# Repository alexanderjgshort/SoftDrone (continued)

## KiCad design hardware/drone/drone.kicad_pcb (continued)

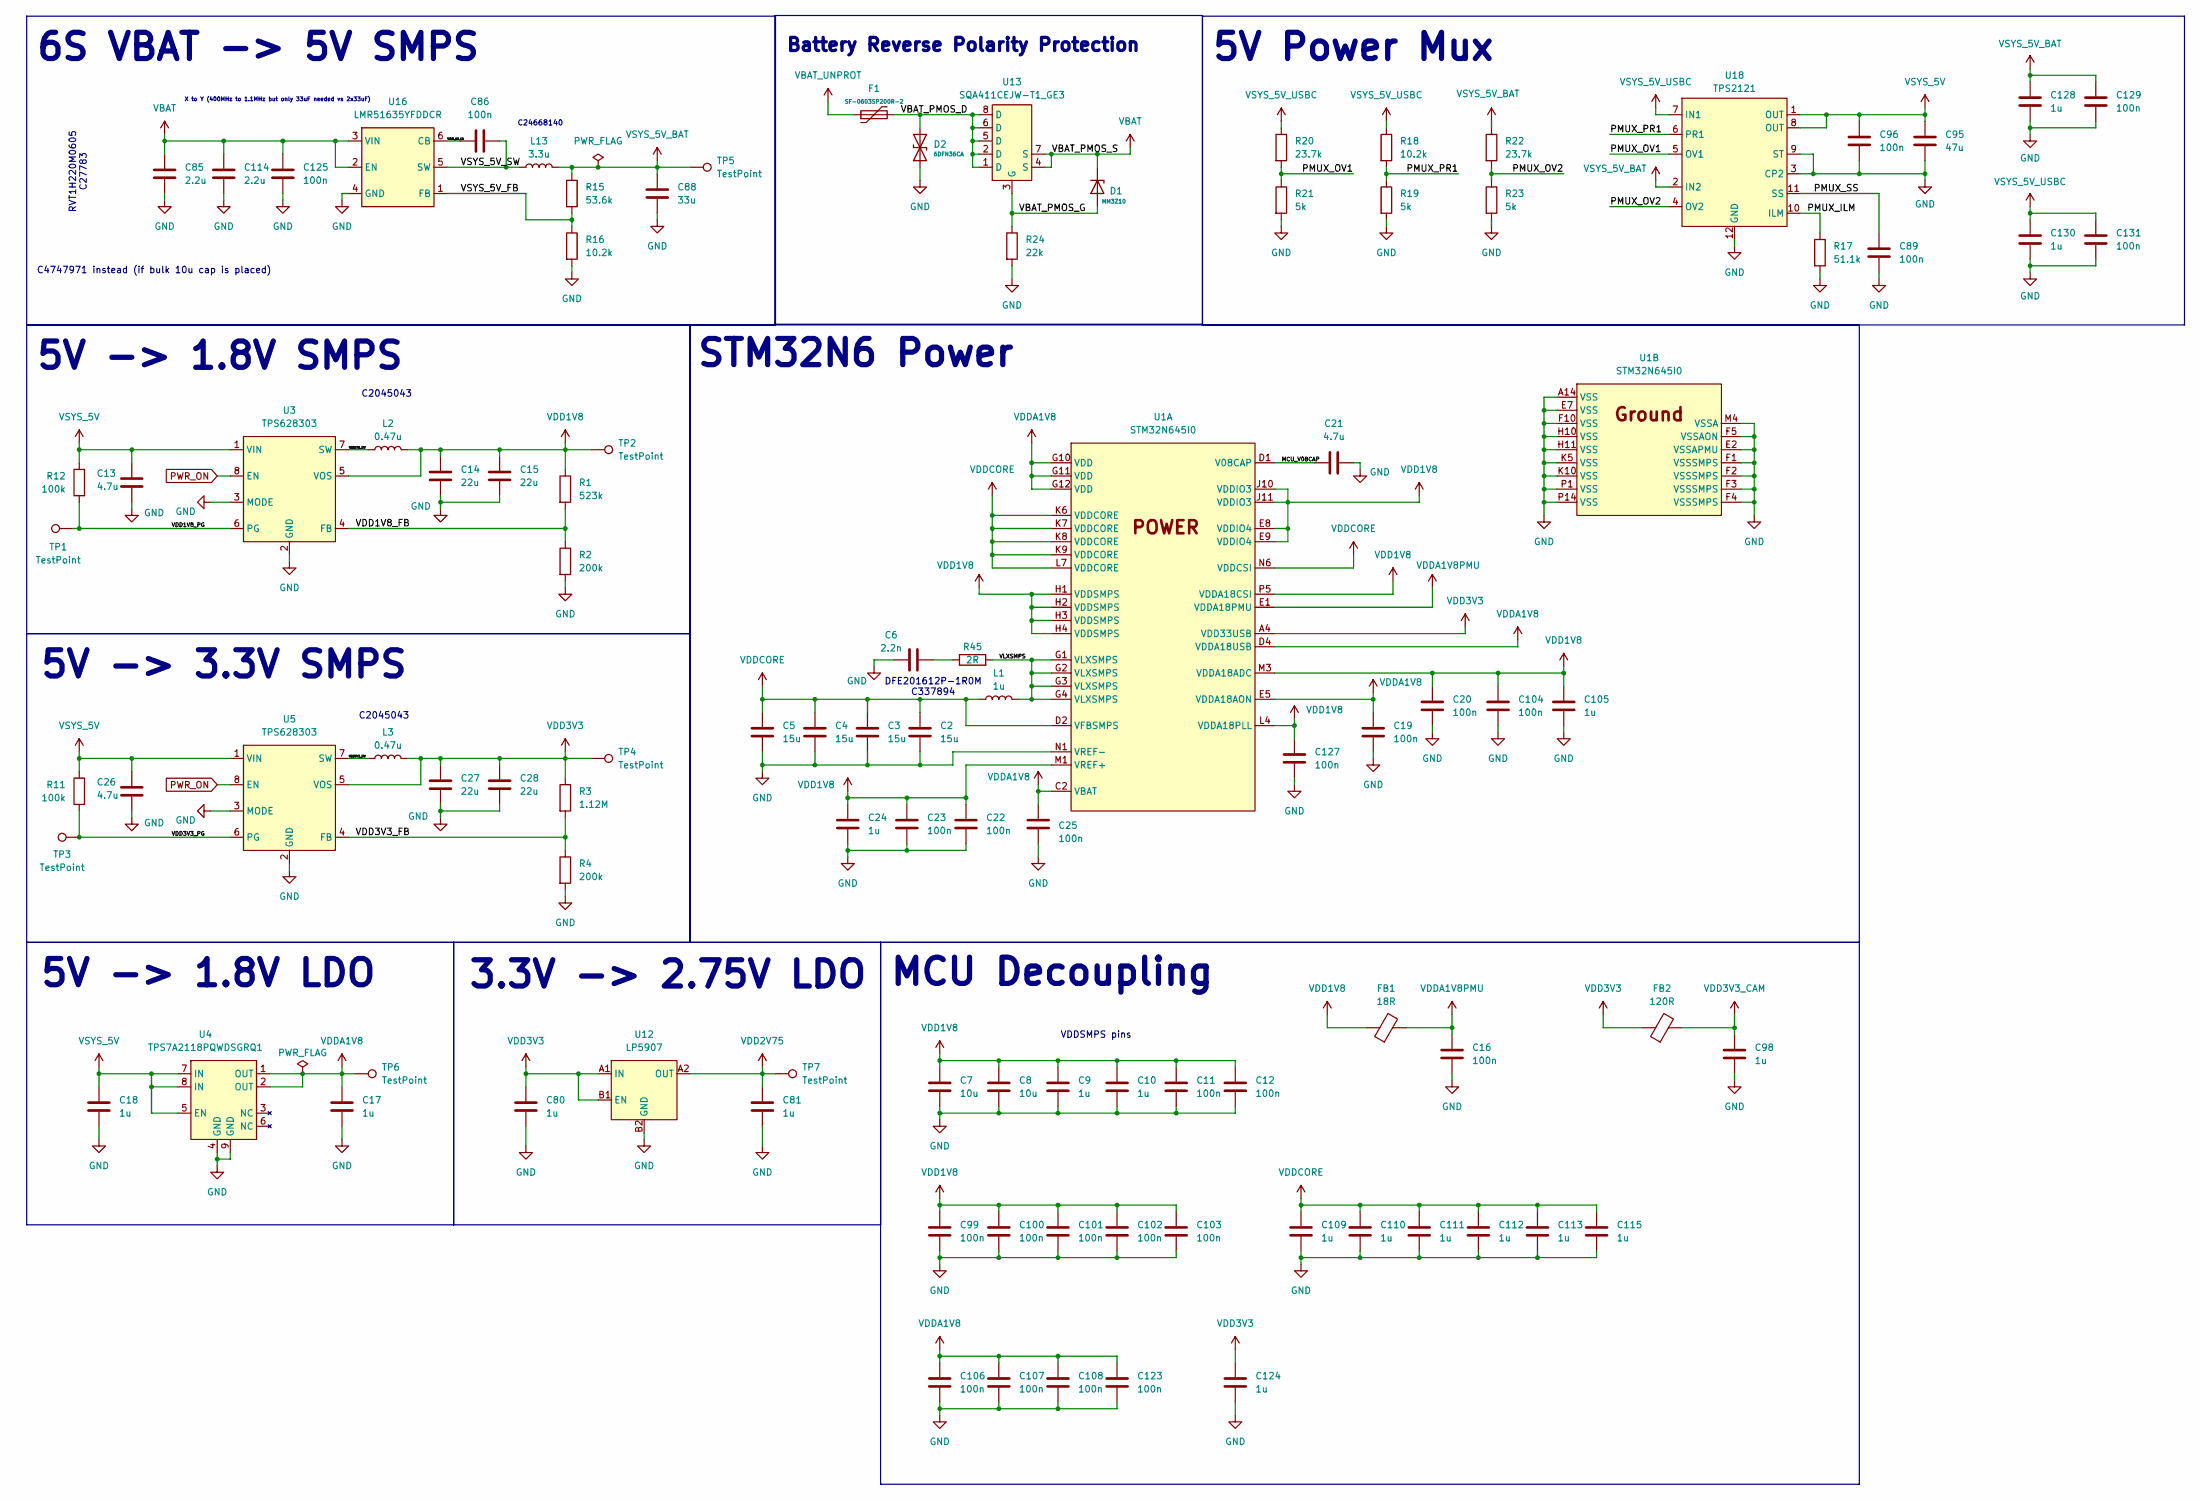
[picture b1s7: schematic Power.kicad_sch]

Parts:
C2, C3, C4, C5: 15u; C_0603_1608Metric
C6: 2.2n; C_0402_1005Metric
C7, C8: 10u; C_0402_1005Metric
C9, C10, C24, C105, C109, C110, C111, C112, C113, C115: 1u; C_0201_0603Metric
C11, C12, C16, C19, C20, C22, C23, C25, C99, C100, C101, C102, C103, C104, C106, C107, C108, C123, C127: 100n; C_0201_0603Metric
C13, C26: 4.7u; C_0603_1608Metric
C14, C15, C27, C28: 22u; C_0603_1608Metric
C17, C18, C80, C81, C128, C130: 1u; C_0603_1608Metric
C21: 4.7u; C_0402_1005Metric
C85, C114: 2.2u; C_1206_3216Metric
C86, C89, C96, C125: 100n; C_0603_1608Metric
C88: 33u; C_1812_4532Metric
C95: 47u; C_1206_3216Metric
C98, C124: 1u; C_0402_1005Metric
C129, C131: 100n; C_0402_1005Metric
D1: MM3Z10; D_SOD-323
D2: 6DFN36CA; 6DFN12CA
F1: SF-0603SP200R-2; Fuse_0603_1608Metric
FB1: 18R; R_0603_1608Metric
FB2: 120R; R_0402_1005Metric
L1: 1u; CVH201610A-2R2M
L2, L3: 0.47u; TFM201610ALC-R47MTAA
L13: 3.3u; 74439324033
R1: 523k; R_0402_1005Metric
R2, R4: 200k; R_0402_1005Metric
R3: 1.12M; R_0402_1005Metric
R11, R12: 100k; R_0402_1005Metric
R15: 53.6k; R_0603_1608Metric
R16: 10.2k; R_0603_1608Metric
R17: 51.1k; R_0402_1005Metric
R18: 10.2k; R_0402_1005Metric
R19, R21, R23: 5k; R_0402_1005Metric
R20, R22: 23.7k; R_0402_1005Metric
R24: 22k; R_0603_1608Metric
R45: 2R; R_0402_1005Metric
TP1, TP2, TP3, TP4, TP5, TP6, TP7: TestPoint; TestPoint_Pad_2.0x2.0mm
U1: STM32N645I0; BGA178C80P14X14_1200X1200X100
U3, U5: TPS628303; WQFN-HR8_RZE_TEX
U4: TPS7A2118PQWDSGRQ1; Texas_DSG0008A_WSON-8-1EP_2x2mm_P0.5mm_EP0.9x1.6mm
U12: LP5907; BGA4C35P2X2_64X64X50
U13: SQA411CEJW-T1_GE3; SQA411CEJWT1_GE3
U16: LMR51635YFDDCR; SOT-23-6
U18: TPS2121; TPS2121RUXT

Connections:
/Power/MCU_V08CAP: C21.2, U1.D1 (V08CAP)
/Power/PMUX_ILM: R17.1, U18.10 (ILM)
/Power/PMUX_OV1: R20.2, R21.1, U18.5 (OV1)
/Power/PMUX_OV2: R22.2, R23.1, U18.4 (OV2)
/Power/PMUX_PR1: R18.2, R19.1, U18.6 (PR1)
/Power/PMUX_SS: C89.1, U18.11 (SS)
/Power/VBAT_PMOS_D: D2.2 (A2), F1.2, U13.1 (D), U13.2 (D), U13.5 (D), U13.6 (D), U13.8 (D)
/Power/VBAT_PMOS_G: D1.2 (A), R24.1, U13.3 (G)
/Power/VDD1V8_FB: R1.2, R2.1, U3.4 (FB)
/Power/VDD1V8_PG: R12.2, TP1.1 (1_1), U3.6 (PG)
/Power/VDD1V8_SW: L2.1, U3.7 (SW)
/Power/VDD3V3_FB: R3.2, R4.1, U5.4 (FB)
/Power/VDD3V3_PG: R11.2, TP3.1 (1_1), U5.6 (PG)
/Power/VDD3V3_SW: L3.1, U5.7 (SW)
/Power/VLXSMPS: L1.2, R45.2, U1.G1 (VLXSMPS), U1.G2 (VLXSMPS), U1.G3 (VLXSMPS), U1.G4 (VLXSMPS)
/Power/VSYS_5V_CB: C86.1, U16.6 (CB)
/Power/VSYS_5V_FB: R15.2, R16.1, U16.1 (FB)
/Power/VSYS_5V_SW: C86.2, L13.1, U16.5 (SW)
GND: C2.2, C3.2, C4.2, C5.2, C6.1, C7.2, C8.2, C9.2, C10.2, C11.2, C12.2, C13.2, C14.2, C15.2, C16.2, C17.2, C18.2, C19.2, C20.2, C21.1, C22.2, C23.2, C24.2, C25.2, C26.2, C27.2, C28.2, C80.2, C81.2, C85.2, C88.2, C89.2, C95.2, C96.2, C98.2, C99.2, C100.2, C101.2, C102.2, C103.2, C104.2, C105.2, C106.2, C107.2, C108.2, C109.2, C110.2, C111.2, C112.2, C113.2, C114.2, C115.2, C123.2, C124.2, C125.2, C127.2, C128.2, C129.2, C130.2, C131.2, D2.1 (A1), R2.2, R4.2, R16.2, R17.2, R19.2, R21.2, R23.2, R24.2, U1.A14 (VSS), U1.E2 (VSSAPMU), U1.E7 (VSS), U1.F1 (VSSSMPS), U1.F2 (VSSSMPS), U1.F3 (VSSSMPS), U1.F4 (VSSSMPS), U1.F5 (VSSAON), U1.F10 (VSS), U1.H10 (VSS), U1.H11 (VSS), U1.K5 (VSS), U1.K10 (VSS), U1.M4 (VSSA), U1.N1 (VREF-), U1.P1 (VSS), U1.P14 (VSS), U3.2 (GND), U3.3 (MODE), U4.4 (GND), U4.9 (GND), U5.2 (GND), U5.3 (MODE), U12.B2 (GND), U16.4 (GND), U18.3 (CP2), U18.9 (ST), U18.12 (GND); also elsewhere on the board
unnamed: C6.2, R45.1
PWR_ON: U3.8 (EN), U5.8 (EN); also elsewhere on the board
VBAT: C85.1, C114.1, C125.1, D1.1 (K), U13.4 (S), U13.7 (S), U16.2 (EN), U16.3 (VIN); also elsewhere on the board
VBAT_UNPROT: F1.1; also elsewhere on the board
VDD1V8: C7.1, C8.1, C9.1, C10.1, C11.1, C12.1, C14.1, C15.1, C20.1, C22.1, C23.1, C24.1, C99.1, C100.1, C101.1, C102.1, C103.1, C104.1, C105.1, C127.1, FB1.1, L2.2, R1.1, TP2.1 (1_1), U1.E8 (VDDIO4), U1.E9 (VDDIO4), U1.H1 (VDDSMPS), U1.H2 (VDDSMPS), U1.H3 (VDDSMPS), U1.H4 (VDDSMPS), U1.J10 (VDDIO3), U1.J11 (VDDIO3), U1.L4 (VDDA18PLL), U1.M1 (VREF+), U1.M3 (VDDA18ADC), U1.P5 (VDDA18CSI), U3.5 (VOS); also elsewhere on the board
VDD2V75: C81.1, TP7.1 (1_1), U12.A2 (OUT); also elsewhere on the board
VDD3V3: C27.1, C28.1, C80.1, C124.1, FB2.1, L3.2, R3.1, TP4.1 (1_1), U1.A4 (VDD33USB), U5.5 (VOS), U12.A1 (IN), U12.B1 (EN); also elsewhere on the board
VDD3V3_CAM: C98.1, FB2.2; also elsewhere on the board
VDDA1V8: C17.1, C19.1, C25.1, C106.1, C107.1, C108.1, C123.1, TP6.1 (1_1), U1.C2 (VBAT), U1.D4 (VDDA18USB), U1.E5 (VDDA18AON), U1.G10 (VDD), U1.G11 (VDD), U1.G12 (VDD), U4.1 (OUT), U4.2 (OUT); also elsewhere on the board
VDDA1V8PMU: C16.1, FB1.2, U1.E1 (VDDA18PMU)
VDDCORE: C2.1, C3.1, C4.1, C5.1, C109.1, C110.1, C111.1, C112.1, C113.1, C115.1, L1.1, U1.D2 (VFBSMPS), U1.K6 (VDDCORE), U1.K7 (VDDCORE), U1.K8 (VDDCORE), U1.K9 (VDDCORE), U1.L7 (VDDCORE), U1.N6 (VDDCSI)
VSYS_5V: C13.1, C18.1, C26.1, C95.1, C96.1, R11.1, R12.1, U3.1 (VIN), U4.5 (EN), U4.7 (IN), U4.8 (IN), U5.1 (VIN), U18.1 (OUT), U18.8 (OUT); also elsewhere on the board
VSYS_5V_BAT: C88.1, C128.1, C129.1, L13.2, R15.1, R22.1, TP5.1 (1_1), U18.2 (IN2)
VSYS_5V_USBC: C130.1, C131.1, R18.1, R20.1, U18.7 (IN1); also elsewhere on the board

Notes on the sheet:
3.3V -> 2.75V LDO
DFE201612P-1R0M C337894
RVT1H220M0605 C27783
5V -> 1.8V LDO
VDDSMPS pins
C2045043
5V Power Mux
MCU Decoupling
Battery Reverse Polarity Protection
C4747971 instead (if bulk 10u cap is placed)
5V -> 3.3V SMPS
6S VBAT -> 5V SMPS
5V -> 1.8V SMPS
X to Y (400MHz to 1.1MHz but only 33uF needed vs 2x33uF)
C24668140
STM32N6 Power

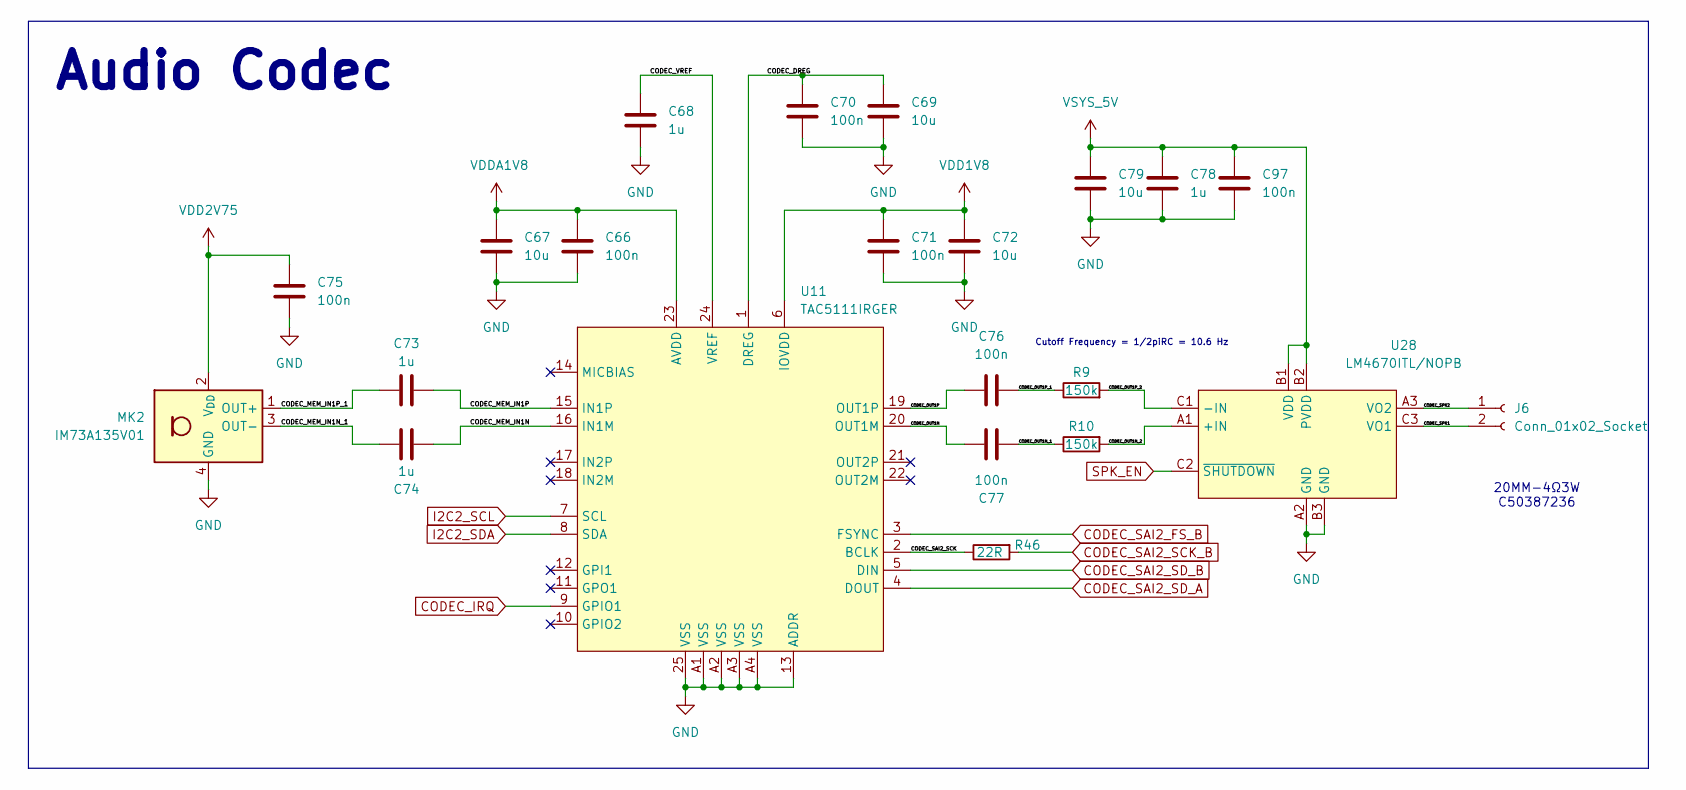
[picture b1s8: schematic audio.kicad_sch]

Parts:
C66, C70, C71, C75, C97: 100n; C_0402_1005Metric
C67, C69, C72, C79: 10u; C_0805_2012Metric
C68: 1u; C_0603_1608Metric
C73, C74, C78: 1u; C_0402_1005Metric
C76, C77: 100n; C_0201_0603Metric
J6: Conn_01x02_Socket; JST_SH_BM02B-SRSS-TB_1x02-1MP_P1.00mm_Vertical
MK2: IM73A135V01; Infineon_PG-LLGA-5-2
R9, R10: 150k; R_0201_0603Metric
R46: 22R; R_0402_1005Metric
U11: TAC5111IRGER
U28: LM4670ITL/NOPB; BGA9C50P3X3_146X148X68

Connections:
/Audio/CODEC_DREG: C69.1, C70.1, U11.1 (DREG)
/Audio/CODEC_MEM_IN1N: C74.2, U11.16 (IN1M)
/Audio/CODEC_MEM_IN1N_1: C74.1, MK2.3 (OUT-)
/Audio/CODEC_MEM_IN1P: C73.2, U11.15 (IN1P)
/Audio/CODEC_MEM_IN1P_1: C73.1, MK2.1 (OUT+)
/Audio/CODEC_OUT1N: C77.2, U11.20 (OUT1M)
/Audio/CODEC_OUT1N_1: C77.1, R10.1
/Audio/CODEC_OUT1N_2: R10.2, U28.A1 (+IN)
/Audio/CODEC_OUT1P: C76.1, U11.19 (OUT1P)
/Audio/CODEC_OUT1P_1: C76.2, R9.1
/Audio/CODEC_OUT1P_2: R9.2, U28.C1 (-IN)
/Audio/CODEC_SAI2_SCK: R46.1, U11.2 (BCLK)
/Audio/CODEC_SPK1: J6.2, U28.C3 (VO1)
/Audio/CODEC_SPK2: J6.1, U28.A3 (VO2)
/Audio/CODEC_VREF: C68.1, U11.24 (VREF)
CODEC_IRQ: U11.9 (GPIO1); also elsewhere on the board
CODEC_SAI2_FS_B: U11.3 (FSYNC); also elsewhere on the board
CODEC_SAI2_SCK_B: R46.2; also elsewhere on the board
CODEC_SAI2_SD_A: U11.4 (DOUT); also elsewhere on the board
CODEC_SAI2_SD_B: U11.5 (DIN); also elsewhere on the board
GND: C66.2, C67.2, C68.2, C69.2, C70.2, C71.2, C72.2, C75.1, C78.2, C79.2, C97.2, MK2.4 (GND), MK2.5 (GND), U11.13 (ADDR), U11.25 (VSS), U11.A1 (VSS), U11.A2 (VSS), U11.A3 (VSS), U11.A4 (VSS), U28.A2 (GND), U28.B3 (GND); also elsewhere on the board
I2C2_SCL: U11.7 (SCL); also elsewhere on the board
I2C2_SDA: U11.8 (SDA); also elsewhere on the board
SPK_EN: U28.C2 (~SHUTDOWN); also elsewhere on the board
VDD1V8: C71.1, C72.1, U11.6 (IOVDD); also elsewhere on the board
VDD2V75: C75.2, MK2.2 (V_{DD}); also elsewhere on the board
VDDA1V8: C66.1, C67.1, U11.23 (AVDD); also elsewhere on the board
VSYS_5V: C78.1, C79.1, C97.1, U28.B1 (VDD), U28.B2 (PVDD); also elsewhere on the board

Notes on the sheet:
Cutoff Frequency = 1/2piRC = 10.6 Hz
20MM-4Ω3W C50387236
Audio Codec

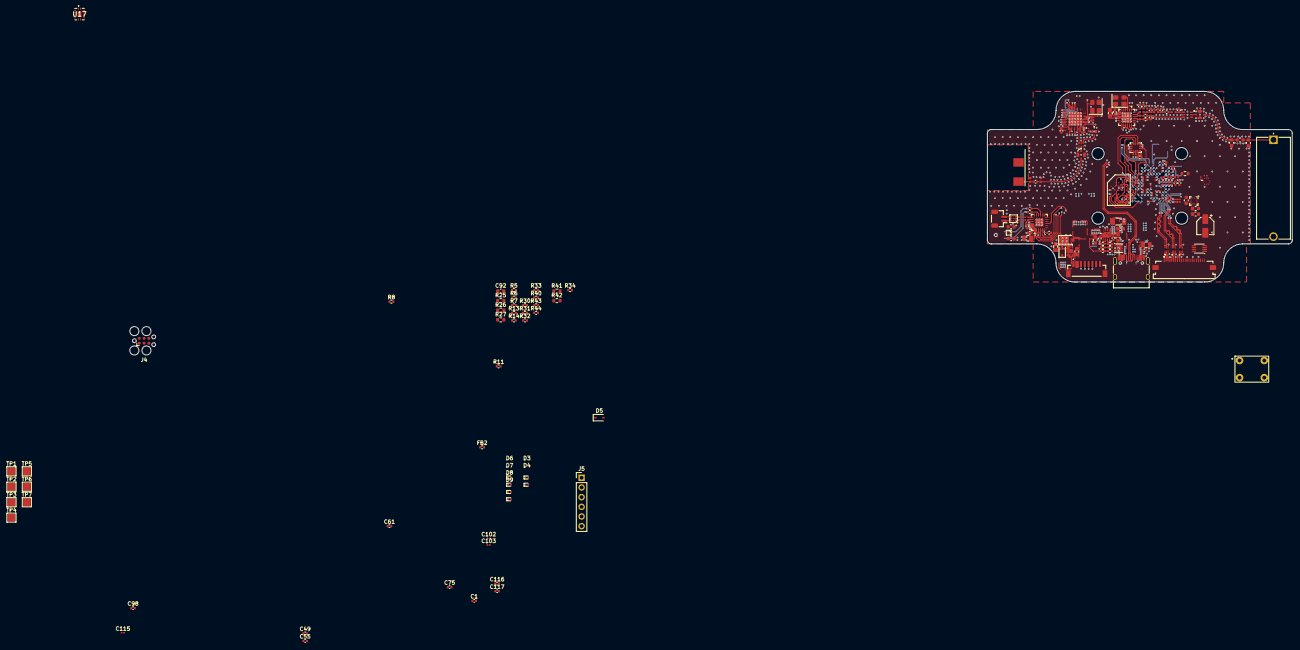
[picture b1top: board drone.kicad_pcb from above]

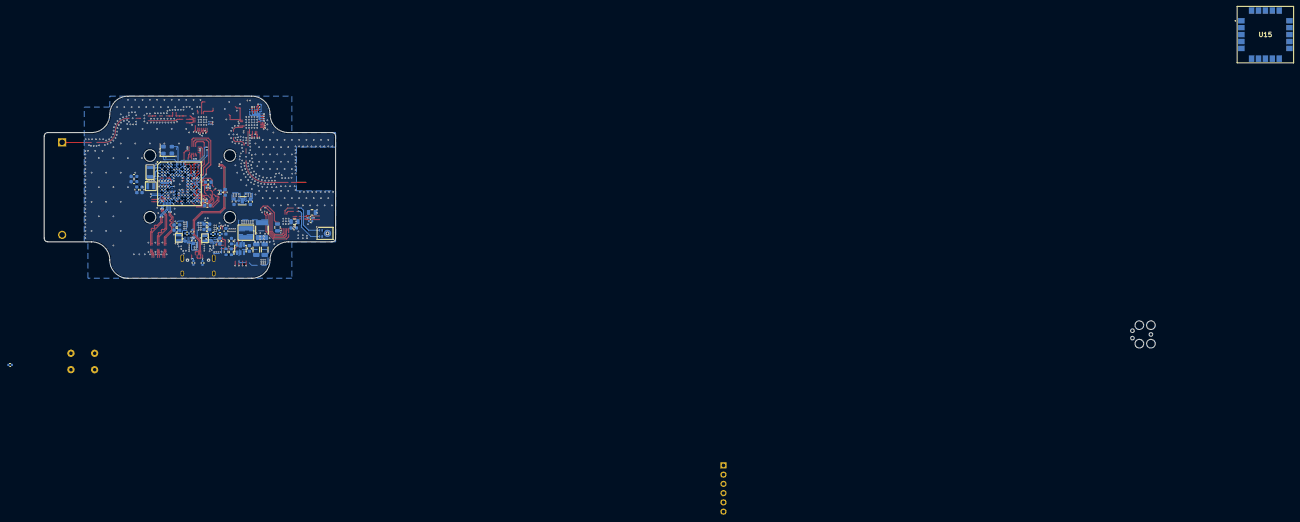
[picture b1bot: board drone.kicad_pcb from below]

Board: 6 copper layers, 80.0 x 50.0 mm, 251 parts (64 on the bottom side), 173 nets.
